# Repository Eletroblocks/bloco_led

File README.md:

# led
Utiliza a energia elétrica recebida para produzir LUZ.

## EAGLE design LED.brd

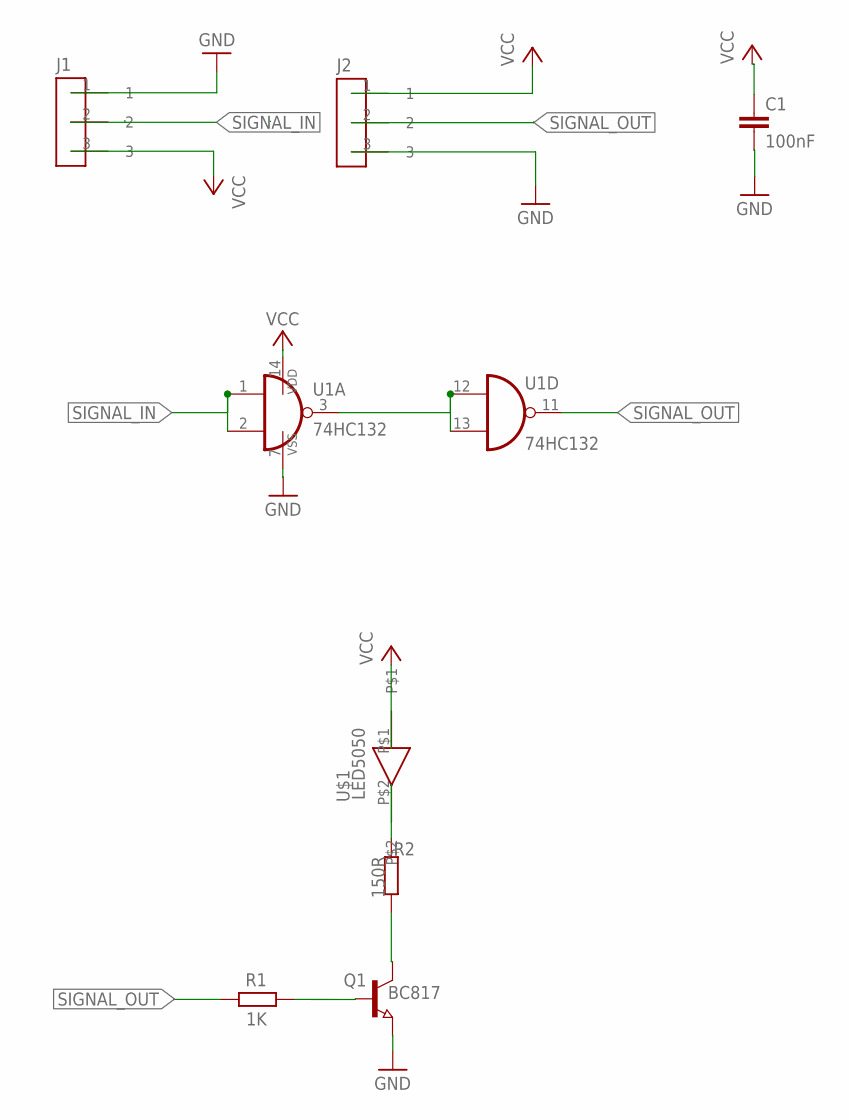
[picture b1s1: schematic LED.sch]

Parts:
C1: 100nF; C0805
J1: CONECTOR_MACHO; MALE
J2: CONECTOR_FEMEA; FEMALE
Q1: BC817; SOT23
R1: 1K; R0805W
R2: 150R; R0805W
U1: 74HC132; SO14
U$1: LED5050

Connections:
GND: C1.2, J1.1, J2.3, Q1.2 (E), U1.7 (VSS)
LED: R2.2, U$1.P$2
unnamed: Q1.1 (B), R1.1
unnamed: U1.3 (O), U1.12 (I0), U1.13 (I1)
unnamed: Q1.3 (C), R2.1
SIGNAL_IN: J1.2, U1.1 (I0), U1.2 (I1)
SIGNAL_OUT: J2.2, R1.2, U1.11 (O)
VCC: C1.1, J1.3, J2.1, U1.14 (VDD), U$1.P$1

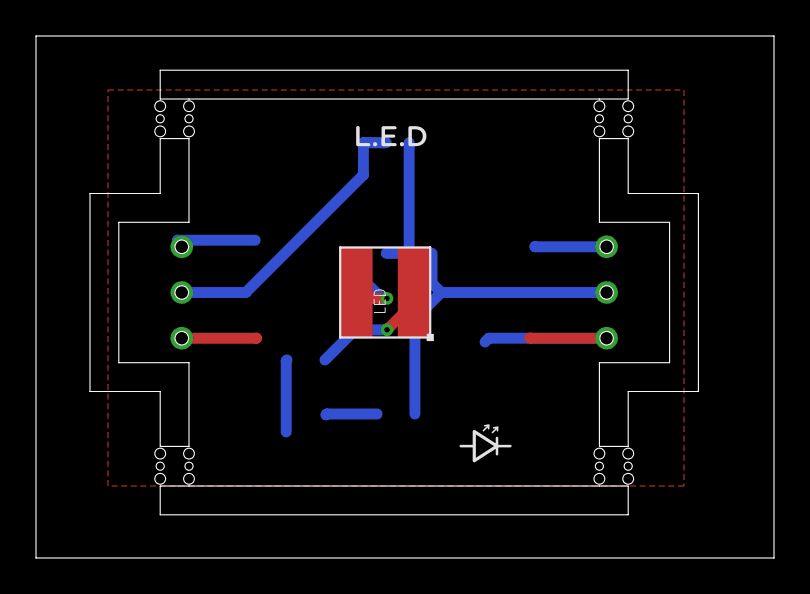
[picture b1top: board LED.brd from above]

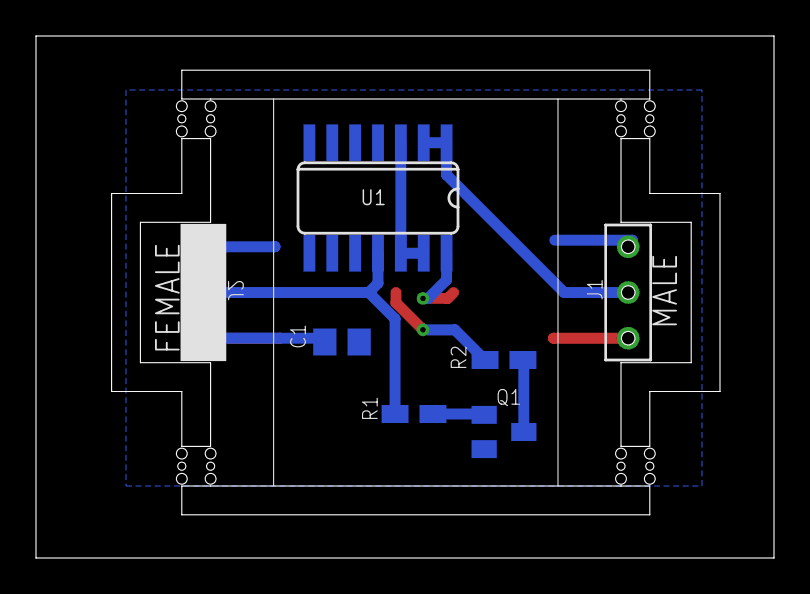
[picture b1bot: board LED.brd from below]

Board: 2 copper layers, 41.0 x 29.0 mm, 12 parts (5 on the bottom side), 8 nets.

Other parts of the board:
U$2, U$3, U$4, U$5: STAMP_DUPLO

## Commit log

2020-11-23 init project
2020-11-23 correção de pads, adição de label para versionamento e plano de VCC
2020-11-23 correção de label
2020-12-28 organizando arquivos
2020-12-28 imagem
2021-03-10 V1.0.3
